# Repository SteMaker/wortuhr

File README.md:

# Wortuhr
Wortuhr basierend auf ESP-12F inkl. Firmware, PCB und Hardware-Beschreibung.

Ich übernehme keinerlei Verantwortung für die Funktionsfähigkeit und Sicherheit dieses Projekts. Jeder, der es nachbaut, ist selbst dafür verantwortlich!

Die Idee und insbesondere die Anordnung der Buchstaben habe ich mir im FabLab Nürnberg abgeschaut. Vielen Dank an der Stelle an den Unbekannten! :)

Die Hardware besteht aus 11 LED-Streifen à 11 LEDs vom Typ WS2812, die RGB fähig sind. Als Controller dient ein ESP-12F (ESP8266), der sich die Uhrzeit über das Internet per NTP holt. Die Konfiguration wird über ein Webinterface vorgenommen. Ein Helligkeitssensor wird verwendet, um die Helligkeit der Uhr (falls gewünscht) automatisch anzupassen. Es gibt auch eine Möglichkeit die Uhr zu einer bestimmten Zeit dunkel zu schalten, und zu einer anderen Zeit wieder zu aktivieren. Außerdem kann man die Farbe der LEDs pro Wort einstellen.

## Weitere Infos und die Bauanleitung sind im [Wiki](https://github.com/SteMaker/wortuhr/wiki)

## Aufbau
Als LED-Streifen werden WS2812 verwendet. Für jede der 11 Zeilen wird ein Streifen mit 11 LEDs verwendet. Die Spannungsversorgung habe ich für jeden Streifen einzeln auf die Hauptplatine gezogen, die Datenleitung muss von `Dout` des einen Streifens zum `Din` des Streifens der nächsten Zeile gezogen werden. Der `Din` der ersten Zeile muss rechts oben liegen und wird mit dem Controller verbunden. Von der linken Seite der ersten Zeile geht dann der `Dout` zum `Din` der linken Seite des zweiten Streifens, usw. Das ist wichtig, da sonst die falschen Buchstaben aufleuchten. Ich verwende LED Streifen mit 60 LEDs pro Meter.

Die Buchstabenmatrix habe ich mit einem 3D-Drucker ausgedruckt. Die STL-Dateien sowie die SVG-Basis liegen im Ordner `rahmen`. Es gibt eine Rückseite, in die die 11 LED-Streifen geklebt werden und eine Vorderseite mit den Aussparungen für die Buchstaben. Das Ganze kommt dann in einen Bilderrahmen. Der IKEA RIBBA 23x23 passt perfekt.

Alternativ kann die Frontplatte aus lackiertem Acrylglas gelasert werden.

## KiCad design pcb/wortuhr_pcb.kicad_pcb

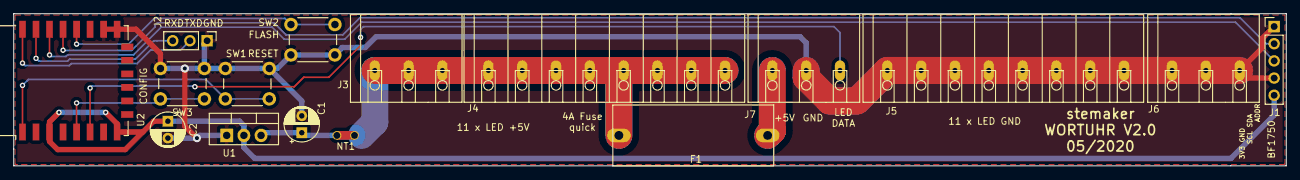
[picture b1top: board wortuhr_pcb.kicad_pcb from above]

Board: 2 copper layers, 188.2 x 22.5 mm, 16 parts (0 on the bottom side), 13 nets.

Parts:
C1, C2: 1µF; CP_Radial_D5.0mm_P2.50mm
F1: Fuse; RND_fuse_holder_5x20mm_horizontal
J1: Conn_01x05_Male; PinHeader_1x05_P2.54mm_Vertical
J2: Conn_01x03_Male; PinHeader_1x03_P2.54mm_Vertical
J3, J6, J7: Conn_01x03_Male; WAGO_250-503
J4, J5: Conn_01x08_Male; WAGO_250-508
NT1: Net-Tie_2; NetTie-2_THT_Pad1.0mm
SW1, SW2, SW3: SW_Push; SW_PUSH_6mm_H4.3mm
U1: LM1117-3.3; TO-220-3_Vertical
U2: ESP-12F; ESP-12E

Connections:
+3V3: C2.1, J1.5, U1.2, U2.3, U2.8
+5V: C1.1, NT1.2, U1.3
/CFG: SW3.1, U2.5
/FLASH: SW2.1, U2.18
/LED_5V: F1.1, J3.1, J3.2, J3.3, J4.1, J4.2, J4.3, J4.4, J4.5, J4.6, J4.7, J4.8, NT1.1
/LED_DATA: J7.3, U2.6
/MAIN_SUPPLY: F1.2, J7.1
/RESET: SW1.2, U2.1
/RXD: J2.3, U2.21
/SCL: J1.3, U2.20
/SDA: J1.2, U2.19
/TXD: J2.2, U2.22
GND: C1.2, C2.2, J1.1, J1.4, J2.1, J5.1, J5.2, J5.3, J5.4, J5.5, J5.6, J5.7, J5.8, J6.1, J6.2, J6.3, J7.2, SW1.1, SW2.2, SW3.2, U1.1, U2.15, U2.16

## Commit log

2020-04-15 Intermediate development version
    - PCB done, awaiting delivery to test
    - FW:
    - WiFi AP to select home WiFi done
    - persistent storage working (WiFi, color, ...)
    - NTP (time retrieval) done
    - LED ctrl done, but not finally tested
2020-04-24 Added documentation
    Need to test now
2020-04-25 Added picture of initial PCB
2020-04-25 Added factory reset and disable softap after 15 mins
2020-04-26 Fixed pattern for VIER
2020-05-02 Support of inactive time window (night off)
2020-05-02 Online update of LED color while moving a slider
    Remove the test button since not needed any more
2020-05-21 Read current time on web i/f, update CRC lib
2020-05-31 New PCB V2
2020-05-31 Neuer Rahmen V2
2020-05-31 move DREI out of DREIVIERTEL
2020-06-01 3D-Druck Rahmen V2, Pics update
2020-06-14 Dimmen nach Umgebungslicht
2020-06-14 reduce default brightness to 50
2020-06-15 fix typo in comment
2020-06-15 pre must be set whenever the word "Uhr" follows the hour
2020-06-15 rename Time.h
    because on Windows it seems to cause a conflict with time.h
2020-06-15 lib ArduinoJson is missing from platoformio.ini
2020-06-15 split environments into ota and initial_upload
2020-06-15 fix activeTimeWindow functionality
2020-06-21 different colors per word
2020-06-28 Potential fix for issue #7
    There is a concurrent call of getTime in main.cpp. Once from the loop,
    once from the async web server. Solution:
    A) Move the time update out of the getTime function and call it only
    from the loop context (explicitly)
    B) Disable interrupts during reading the time, use old value in getTime
    in case an update is ongoing
2020-06-29 make all colours adjustable
2020-07-01 fix large webpage handling by using send_P() instead of send()
2020-07-01 stop printing the WiFi passkey
2020-07-01 now with instant color change from webpage (luma scaling TBD)
2020-07-02 code cleanup & fix loading the colours into browser
2020-07-05 Fixed bug in getting and setting color
2020-07-05 Fixed missing break in LedCtrl.h
2020-07-05 EXPERIMENTAL: show IP address
2020-07-21 enable brightness scaling
2020-07-21 auto detection of BH1750 and TSL2561 brightness sensors
2020-08-02 Switched to HSV for color selection
2020-08-04 TSL2651: longer integration time
2020-08-04 moving average for brightness
2020-12-04 add pictures
2020-12-04 pictures
2020-12-05 more pics
2020-12-05 update pic
2020-12-05 show "WLAN" in blue color while in AP mode
2020-12-06 REAMDME.md: move details to the Wiki
2020-12-06 add pic
2020-12-06 typos
    thanks @flohei
2020-12-18 show IP address in AP mode
2020-12-18 show non-leading zeros in IP address
2020-12-19 checkbox for showIp
    enabled by default
2020-12-23 reference picture in description
2021-08-13 stick to Arduino Core 2.x
    Arduino Core 3.x has breaking changes and FastLED does not behave well
    https://github.com/platformio/platform-espressif8266/releases/tag/v3.0.0
2021-08-13 calculation of daylight saving time
    calculation based on https://github.com/andydoro/DST_RTC
2021-08-27 add favicon
    icon drawn by myself and converted using https://www.mobilefish.com/services/base64/base64.php
2022-03-27 Fixed usage of vue@2
2022-04-03 avoid issues with latest framework and FastLED
    Framework 3.x seems to have higher IRQ load from WiFi
    - double FastLED.show() because sometimes it does not update
    - suppress register warnings
2022-07-24 added button 'LED-Test' to config page
2022-07-24 allow using the configuration button during connection attempt
2022-09-16 Minor improvement
    Replaced hard coded amount of patterns with compile time calc
